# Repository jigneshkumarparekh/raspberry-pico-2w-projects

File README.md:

# Raspberry Pi Pico 2w Projects

This repository contains various projects and examples for the Raspberry Pi Pico 2w microcontroller.

## Projects Included

- **pico2w_HBridge_motor** - H-Bridge motor control projects
- **pico2w_led_test** - LED testing and external LED control
- **pico2w_temp_sensor** - Temperature sensor projects
- **pico2w-motion-sensor** - Motion sensor projects
- **pic2w-servo-example** - Servo control example

## Getting Started

Each project folder contains its own implementation files and documentation. Navigate to the specific project folder for more details and wiring diagrams.

## Requirements

- Raspberry Pi Pico 2w
- MicroPython firmware
- Appropriate sensors/components for each project

## Usage

Refer to individual project folders for specific instructions and wiring diagrams.

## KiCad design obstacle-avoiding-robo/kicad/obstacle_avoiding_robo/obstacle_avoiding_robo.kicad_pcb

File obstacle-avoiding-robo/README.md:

# Obstacle-Avoiding Robo Car (Pico 2 W + TB6612FNG)

An obstacle-avoiding robo car using Raspberry Pi Pico 2 W, TB6612FNG dual H-Bridge, and an HC-SR04 ultrasonic sensor. Two ready-to-flash variants are included:

- Single motor: Reverse-until-safe behavior using the left motor only. See [single_motor_main.py](single_motor_main.py).
- Dual motor: Reverse, then turn-in-place with simple validation before resuming. See [dual_motor_main.py](dual_motor_main.py).

Both variants are MicroPython-based and blink the onboard LED while running.

Here is the link to the video: https://youtube.com/shorts/muM9jOU0rGQ?feature=share

## Features

- Obstacle detection: HC-SR04 distance measurement with adaptive slowdown near obstacles.
- Smooth PWM control: 0–100% speed mapped to PWM at 10 kHz; ramped speed changes.
- Two variants: Single-motor reverse-only and dual-motor reverse+turn with retries.
- Safe defaults: Reverse safety timeout; driver disabled on stop.

## Hardware

- Board: Raspberry Pi Pico 2 W (MicroPython).
- Motor driver: TB6612FNG (dual channel A/B) with STBY standby pin.
- Motors: 1× DC motor (single) or 2× DC motors (dual).
- Sensor: HC-SR04 ultrasonic.
- Power: VM (motors/battery), VCC (logic). Common ground required between Pico, driver, and sensor.

## Wiring

- Diagrams
  - Single-motor: [Obstacle_avoiding_robo_car_wiring_single_motor.png](Obstacle_avoiding_robo_car_wiring_single_motor.png)
  - Dual-motor: [Obstacle_avoiding_robo_car_wiring_dual_motor.png](Obstacle_avoiding_robo_car_wiring_dual_motor.png)
- Reference: Existing Miro wiring board link (kept for additional clarity): https://miro.com/app/board/uXjVGOnAl5s=/?share_link_id=999963932204
- Notes
  - Tie grounds: Pico GND, TB6612FNG GND, sensor GND, and battery negative.
  - TB6612FNG STBY must be driven high to enable outputs.
  - If HC-SR04 runs at 5 V, ensure the Echo signal to the Pico is 3.3 V safe (divider/level shifter).
  - Motor polarity may need swapping to match “forward” with the code.

## Pin Map (GPIO)

- Common
  - STBY: 12
  - TRIG: 16
  - ECHO: 17
  - LED: onboard (“LED”)
- Single motor (left / channel A) — [single_motor_main.py](single_motor_main.py)
  - LEFT_PWM: 15
  - LEFT_IN1: 14
  - LEFT_IN2: 13
- Dual motor (adds right / channel B) — [dual_motor_main.py](dual_motor_main.py)
  - RIGHT_PWM: 8
  - RIGHT_IN1: 7
  - RIGHT_IN2: 6

## Quick Start

1) Flash MicroPython on Pico 2 W and wire according to the diagram for your variant.
2) Copy the chosen file to the Pico and name it `main.py` to auto-run on power.
   - Single motor: [single_motor_main.py](single_motor_main.py)
   - Dual motor: [dual_motor_main.py](dual_motor_main.py)
3) Power on; the onboard LED will blink as the script runs.

## Setup / Flashing

- Install MicroPython on the Pico 2 W (via Thonny or UF2 drag-and-drop).
- Choose your variant and rename it to `main.py` on the Pico filesystem to auto-run on boot.
- On boot, the onboard LED blinks as the script runs.

## How to Run

- Default demo: Each script calls `simplified_run(20000)` to run ~20 seconds, then stop and disable the driver.
- Continuous operation (recommended):
  - Increase the time limit in the final `simplified_run(...)` call (e.g., use a large value for multi-minute runs), or
  - Edit the script to loop indefinitely before flashing as `main.py`.
- Expected behavior
  - Single motor: Forward cruise, adaptive slowdown near obstacles, reverse-until-safe, then resume.
  - Dual motor: Stop → reverse-until-safe → turn-in-place (alternating direction with validation/retry) → resume.

## Tuning / Calibration

- Shared (both scripts)
  - THRESHOLD_CM: Start avoidance below this distance (single: ~30; dual: ~50 by default).
  - CRUISE_SPEED: Forward speed (0–100%).
  - REVERSE_SPEED: Reverse speed (0–100%).
  - MAX_REVERSE_MS: Safety cap for maximum reverse duration.
  - Ramps and cadence: RAMP_TIME_MS, DECEL_RAMP_MS, RESUME_RAMP_MS, ADAPTIVE_THRESHOLD_MULT, LOOP_DELAY_MS.
- Dual-only (in [dual_motor_main.py](dual_motor_main.py))
  - Turning: TURN_MS, TURN_SPEED, TURN_RAMP_MS, TURN_SETTLE_MS.
  - Validation: TURN_MAX_RETRIES, TURN_VALIDATION_PAUSE_MS.
  - Cruise hysteresis: CRUISE_HYSTERESIS_FACTOR reduces re-ramping chatter near target speed.

## Troubleshooting

- Motors don’t move:
  - Ensure STBY is high; verify VM battery and common ground; confirm PWM pin mapping.
- Jerky/weak motion:
  - Check battery current capability and wiring; the default 10 kHz PWM is fine for most drivers; verify mechanical drag.
- Wrong direction:
  - Swap motor leads or swap IN1/IN2 wiring on the corresponding channel.
- Sensor reads 0 or times out:
  - Verify TRIG and ECHO wiring and sensor power; make Echo 3.3 V safe when powering HC-SR04 from 5 V; avoid very close ranges (<2–3 cm).
- Random resets:
  - Power brownouts under stall; use a capable battery, add bulk and ceramic decoupling near the TB6612FNG.

## Safety & Power

- Separate VM (motors) and VCC (logic) per TB6612FNG guidelines; always share ground.
- Add bulk and ceramic decoupling near the motor driver.
- Respect motor stall current and thermal limits on the driver.

## Files

- Single-motor variant: [single_motor_main.py](single_motor_main.py)
- Dual-motor variant: [dual_motor_main.py](dual_motor_main.py)
- Wiring diagrams:
  - [Obstacle_avoiding_robo_car_wiring_single_motor.png](Obstacle_avoiding_robo_car_wiring_single_motor.png)
  - [Obstacle_avoiding_robo_car_wiring_dual_motor.png](Obstacle_avoiding_robo_car_wiring_dual_motor.png)

Notes

- Removed references to non-existent files (separate main.py source, main_original.py, drive_and_avoid.py, pins.py, test.py) and aligned docs to the two actual variant scripts.

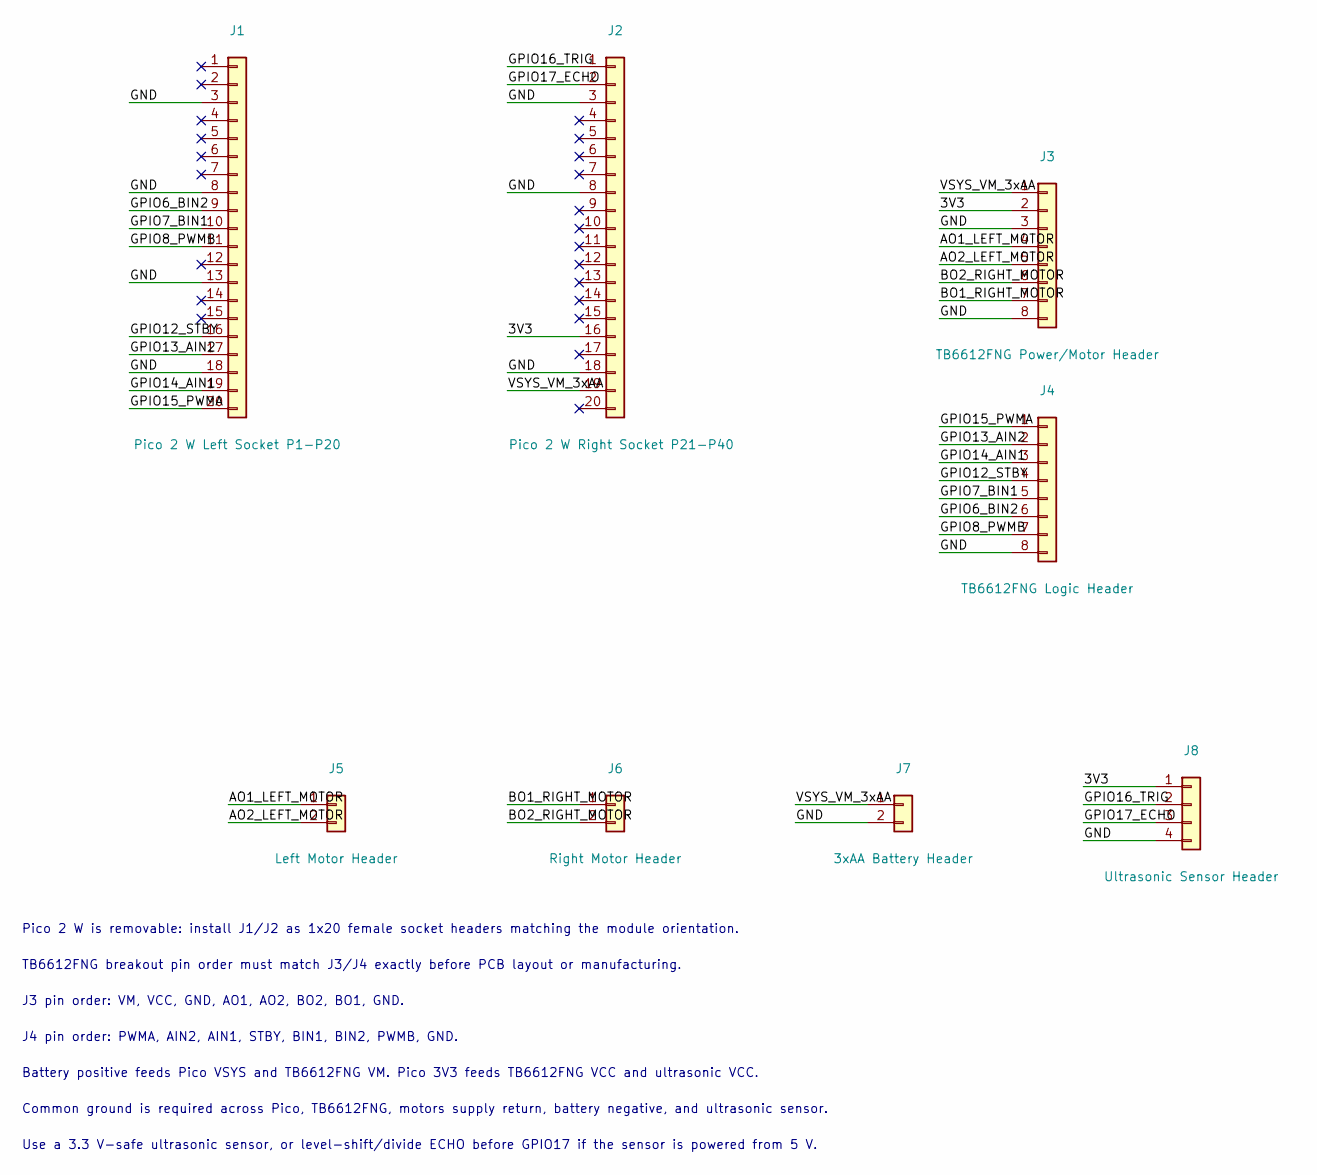
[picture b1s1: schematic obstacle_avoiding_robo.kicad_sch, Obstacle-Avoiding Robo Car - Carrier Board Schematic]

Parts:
J1: Pico 2 W Left Socket P1-P20; PinSocket_1x20_P2.54mm_Vertical
J2: Pico 2 W Right Socket P21-P40; PinSocket_1x20_P2.54mm_Vertical
J3: TB6612FNG Power/Motor Header; PinHeader_1x08_P2.54mm_Vertical
J4: TB6612FNG Logic Header; PinHeader_1x08_P2.54mm_Vertical
J5: Left Motor Header; PinHeader_1x02_P2.54mm_Vertical
J6: Right Motor Header; PinHeader_1x02_P2.54mm_Vertical
J7: 3xAA Battery Header; PinHeader_1x02_P2.54mm_Vertical
J8: Ultrasonic Sensor Header; PinHeader_1x04_P2.54mm_Vertical

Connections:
/3V3: J2.16, J3.2, J8.1
/AO1_LEFT_MOTOR: J3.4, J5.1
/AO2_LEFT_MOTOR: J3.5, J5.2
/BO1_RIGHT_MOTOR: J3.7, J6.1
/BO2_RIGHT_MOTOR: J3.6, J6.2
/GND: J1.3, J1.8, J1.13, J1.18, J2.3, J2.8, J2.18, J3.3, J3.8, J4.8, J7.2, J8.4
/GPIO6_BIN2: J1.9, J4.6
/GPIO7_BIN1: J1.10, J4.5
/GPIO8_PWMB: J1.11, J4.7
/GPIO12_STBY: J1.16, J4.4
/GPIO13_AIN2: J1.17, J4.2
/GPIO14_AIN1: J1.19, J4.3
/GPIO15_PWMA: J1.20, J4.1
/GPIO16_TRIG: J2.1, J8.2
/GPIO17_ECHO: J2.2, J8.3
/VSYS_VM_3xAA: J2.19, J3.1, J7.1

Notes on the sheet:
Pico 2 W is removable: install J1/J2 as 1x20 female socket headers matching the module orientation.
TB6612FNG breakout pin order must match J3/J4 exactly before PCB layout or manufacturing.
J3 pin order: VM, VCC, GND, AO1, AO2, BO2, BO1, GND.
J4 pin order: PWMA, AIN2, AIN1, STBY, BIN1, BIN2, PWMB, GND.
Battery positive feeds Pico VSYS and TB6612FNG VM. Pico 3V3 feeds TB6612FNG VCC and ultrasonic VCC.
Common ground is required across Pico, TB6612FNG, motors supply return, battery negative, and ultrasonic sensor.
Use a 3.3 V-safe ultrasonic sensor, or level-shift/divide ECHO before GPIO17 if the sensor is powered from 5 V.

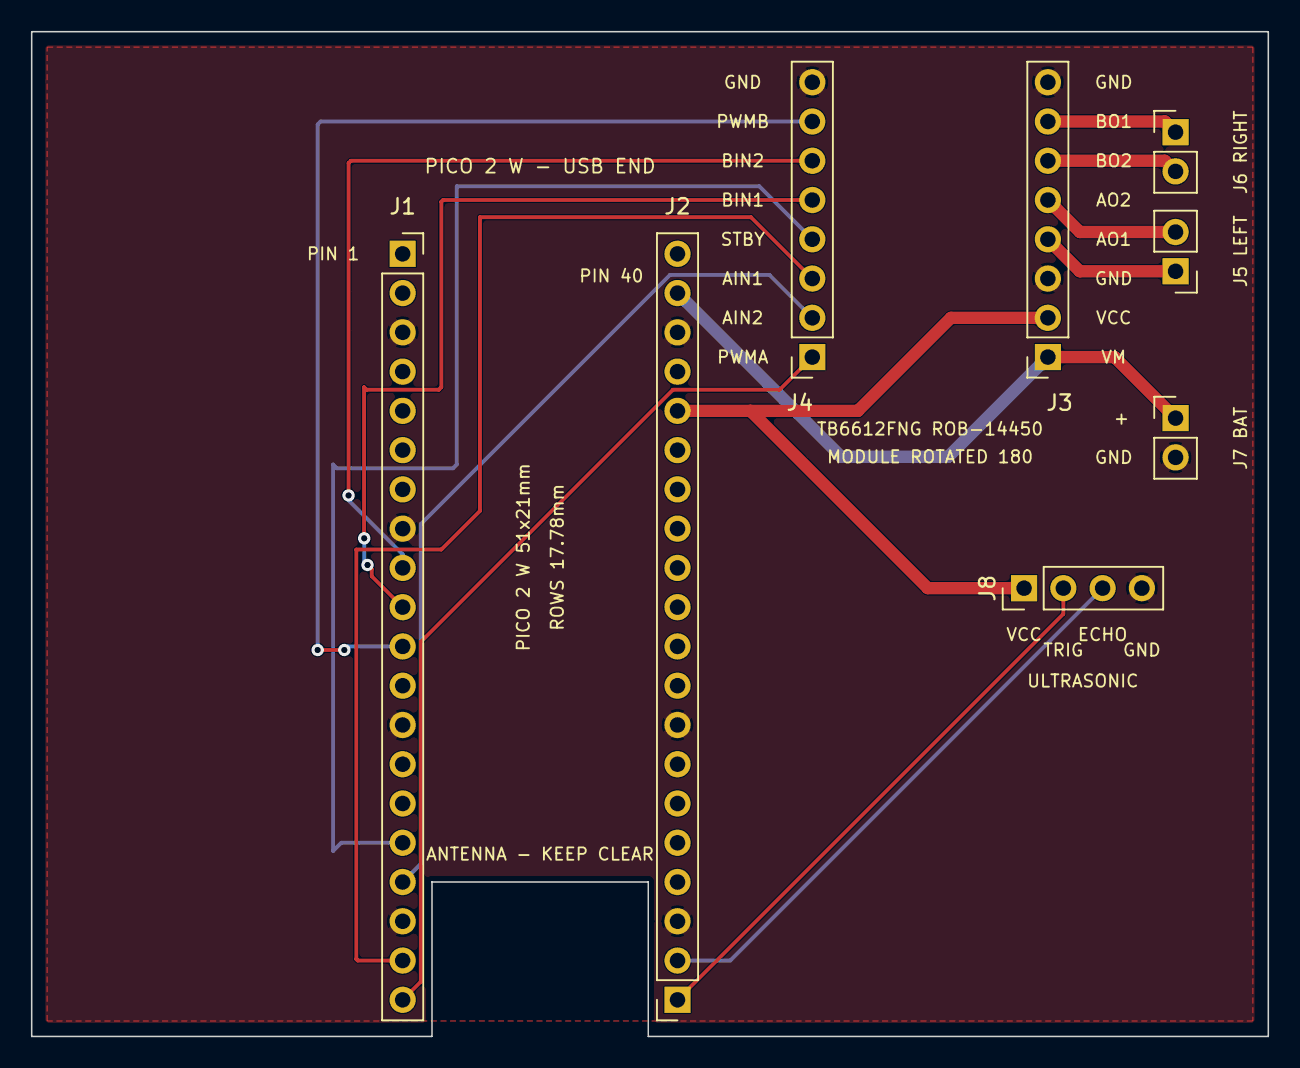
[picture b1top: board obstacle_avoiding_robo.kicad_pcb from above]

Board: 2 copper layers, 80.0 x 65.0 mm, 8 parts (0 on the bottom side), 16 nets.

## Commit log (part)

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2025-12-07 Initial commits
2025-12-07 Added pics for wiring for LED and Motion sensor projects
2025-12-08 Added README for each individual projects
2025-12-15 Created example for Raspberry Pi Pico 2w with servo motor
2025-12-15 Updated readme file
2025-12-15 Added pics for Pico 2w with servo
2025-12-21 Successful connection of TT Motor with Pico2w via TB6612FNG H-Bridge Motor Driver
2025-12-24 Rearrange the folder structure
2025-12-25 HCSR05 Ultrasonic distance sensor connection to pico 2W
2025-12-25 Updated doc for SR05
2025-12-28 Added simple onboard LED test
2026-01-03 WIP: Obstacle avoiding robo
2026-01-17 Obstacle avoiding robocar: Added README file
2026-01-18 Obstacle avoiding car: added wiring diagram
2026-01-24 Updated cruise speed and distance thresold
2026-01-25 Updated code to make reverse motion more smoother
2026-01-25 Added image for car chasis design
2026-02-15 Added separate files for single and dual motor robocar
2026-02-15 Removed unwanted file
2026-02-22 Added mira diagram for dual motor
2026-02-28 Improving car movement to make it more smoother
2026-03-02 Remved outdated files and updated README
2026-03-08 Implement peek-and-choose turn selection with 180° escape
2026-03-09 Updated run time from 20s -> 60s
2026-03-15 Added link to youtube video for Obstacle avoiding robo car
2026-06-28 Generated KiCad schematics for the obstacle avoiding dual motor robo
2026-06-28 Step 2: PCB Ready schematic
